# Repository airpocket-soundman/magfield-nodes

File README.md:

# magfield-nodes

> Magnetic-field visualization with ~100 coin-cell-sized LED nodes — a grid of tiny boards that turn invisible magnetic-field distortion into light.
> コインセル大の小さな基板を約100個並べ、目に見えない磁場の歪みや揺らぎを「光の色」として見える化するプロジェクトです。

## 概要

ボタン電池くらいの小さな基板（ノード）に、地磁気センサー・小さなマイコン・RGB LEDを載せ、磁場の向きや強さに応じてLEDの色をリアルタイムに変えます。この基板を10メートル四方に1メートル間隔で約100個並べると、その空間の中で磁場がどう歪んでいるか・揺らいでいるかが、光の分布として目で見えるようになります。

## ノード基板（v3）

### 主な仕様

| 項目 | 内容 |
|---|---|
| 基板サイズ | 32 × 32 mm、2層、表面実装は片面のみ（コネクタと電池ホルダーは裏面） |
| マイコン | ATtiny1616-MNR（電池直結で動作、書き込みはUPDI） |
| 地磁気センサー | Bosch BMM150（I2C、3.0V LDOレールから給電） |
| LED | WS2812B-MINI ×1（磁場の向き・変化を色で表示） |
| 電池 | LIR2032 充電式コインセル（約40mAh、公称3.6/3.7V）※LCSCに取り扱いがないため別途調達 |
| 電池保護 | DW01A + FS8205A（過放電保護を全ノードに搭載） |
| 電池ホルダー | MYOUNG MY-2032-10（裏面） |
| 接続 | JST PH 4ピン（Grove互換形状、裏面・下辺）: GND / 充電(VBAT) / UPDI / ID予備 |

### 設計のポイント

- **充電は基板側に載せない**: 充電管理は外部の充電ボード側に集約し、ノードは充電中は電源OFF。充電ラインは負荷スイッチの手前から取るため、充電中は充電回路だけが電池につながります。
- **磁気的な配慮**: センサーは電流経路・電池から最も遠い基板の角に配置し、LED（最大電流源）の配線ループ面積を小さくしています。基板自身が作る磁場のオフセットは、ノードごとの校正で吸収する前提です。
- **書き込み**: UPDIパッド（表面）とJST PHコネクタ経由の両方から書き込み可能。専用書き込み機なしで済むよう、充電ボード経由の書き込みも計画しています。

詳細は [node/DESIGN.md](node/DESIGN.md) を参照してください。

## 充電ボード（ハブ、WIP）

ノード10台をまとめて充電・管理するボードです。頭脳は持たせず、M5StackからPort A（I2C）経由で制御する構成にしています。

- 充電IC ×10（MCP73831、約40mA = 1C）、80〜90%で止めるカットオフ制御
- I2C GPIOエクスパンダ＋アナログ切替＋I2C ADCで、全チャンネルの状態監視と電池電圧読み取り
- UPDI信号の切替により、差したノードへのプログラム書き込みにも対応予定
- 充電用電源はボード側のUSB-C 5V入力から供給

KiCadファイル一式は [charge-board/](charge-board/) に追加済みです（4層基板、WIP — DRC残件あり、未発注。現状は charge-board/DESIGN.md 参照）。

## ステータス（2026-10-30時点）

- ノード基板 v3: 設計完了（KiCad 8、DRCエラー0・未接続0）。**未発注** — 発注前に要確認の項目が [node/DESIGN.md](node/DESIGN.md) に残っています（FS8205Aのピン配置、ホルダーのランドパターン、WS2812B-MINIのパッド順、LDOとスライドスイッチのLCSC型番など）。
- 充電ボード: KiCadファイル追加済み（4層、WIP）。DRC残件（未接続1件・クリアランス4件）があり未発注。
- ファームウェア（ノード／M5Stack側とも）: 未着手。要件はDESIGN.mdに記録しています（常時点灯／点滅モード、感度マッピングのパラメータ化など）。

## リポジトリ構成

```
.
├── README.md            このファイル
├── LICENSE              MIT
├── bom-estimate.md      ノード基板のBOM見積もり（LCSC価格ベース）
├── node/                ノード基板 (KiCad 8)
│   ├── magfield-node.kicad_pro / .kicad_sch / .kicad_pcb
│   ├── DESIGN.md        設計仕様・判断記録・未確認事項
│   ├── MAGFIELD.pretty/ カスタムフットプリント（基板埋め込み分から復元）
│   ├── fp-lib-table
│   ├── gerbers/         製造用ガーバー（v3）
│   └── iterations/      レイアウト図・外観図
└── charge-board/        充電ボード（ハブ、KiCadファイル一式、WIP）
```

## ライセンス

MIT License — [LICENSE](LICENSE) を参照してください。

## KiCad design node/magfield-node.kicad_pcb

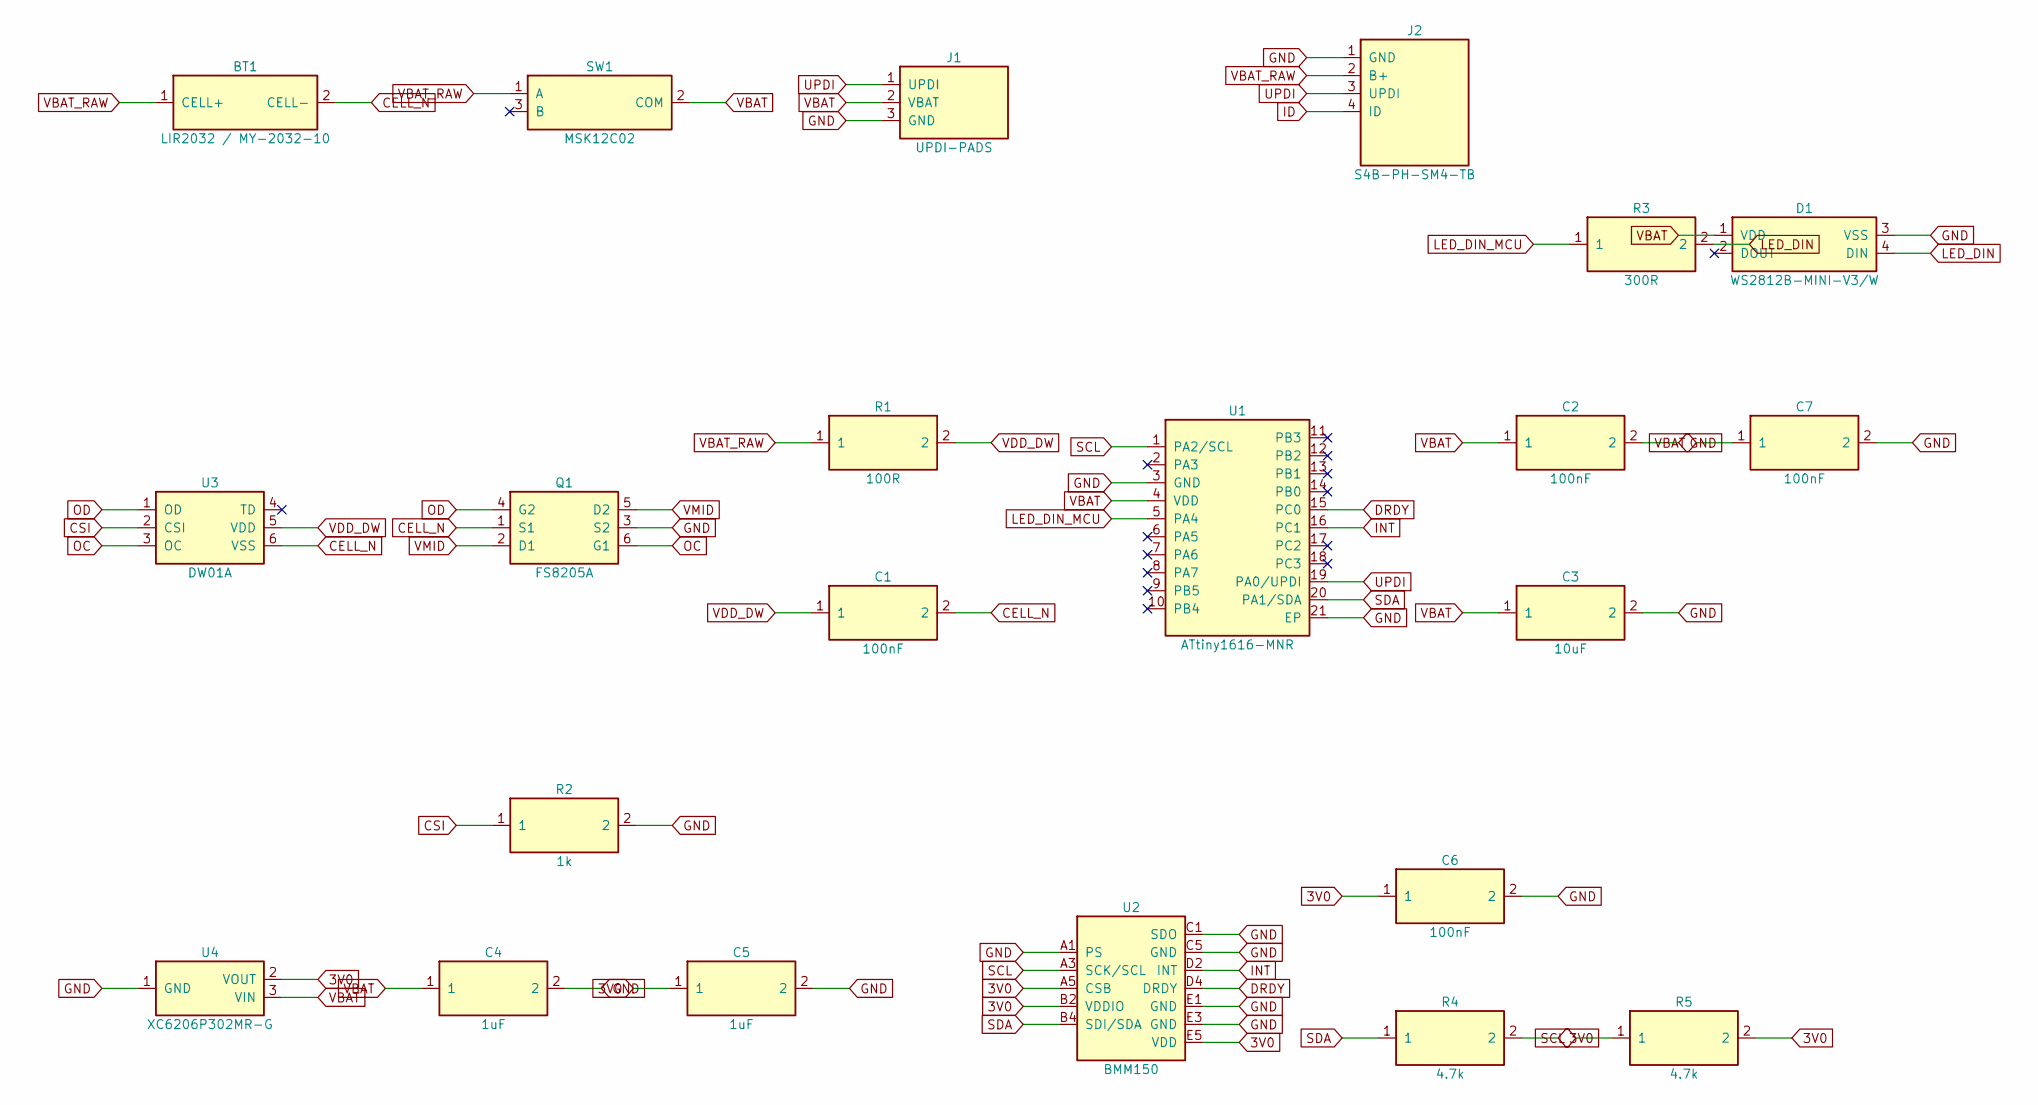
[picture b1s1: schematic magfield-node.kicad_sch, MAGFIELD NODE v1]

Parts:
BT1: LIR2032 / MY-2032-10; MY-2032-10; MPN MY-2032-10; LCSC C964827
C1, C2, C6, C7: 100nF; C_0603_1608Metric; MPN CL10B104KB8NNNC; LCSC C1591
C3: 10uF; C_0603_1608Metric; MPN CL10A106KP8NNNC; LCSC C19702
C4, C5: 1uF; C_0603_1608Metric; MPN CL10A105KB8NNNC; LCSC C15849
D1: WS2812B-MINI-V3/W; WS2812B-MINI; MPN WS2812B-MINI-V3/W; LCSC C527089
J1: UPDI-PADS; UPDI_PADS
J2: S4B-PH-SM4-TB; JST_PH_S4B-PH-SM4-TB_1x04-1MP_P2.00mm_Horizontal; MPN S4B-PH-SM4-TB(LF)(SN); LCSC C265102
Q1: FS8205A; SOT-23-6; MPN FS8205A; LCSC C2830320
R1: 100R; R_0603_1608Metric; MPN 0603WAF1000T5E; LCSC C22775
R2: 1k; R_0603_1608Metric; MPN 0603WAF1001T5E; LCSC C21190
R3: 300R; R_0603_1608Metric; MPN 0603WAF3000T5E; LCSC C23025
R4, R5: 4.7k; R_0603_1608Metric; MPN 0603WAF4701T5E; LCSC C23162
SW1: MSK12C02; SW_MSK12C02; MPN MSK12C02; LCSC C431540
U1: ATtiny1616-MNR; VQFN-20-1EP_3x3mm_P0.4mm_EP1.7x1.7mm; MPN ATTINY1616-MNR; LCSC C507118
U2: BMM150; BMM150_WLCSP12; MPN BMM150; LCSC C171681
U3: DW01A; SOT-23-6; MPN DW01A; LCSC C42459937
U4: XC6206P302MR-G; SOT-23; MPN XC6206P302MR-G; LCSC C9972

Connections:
3V0: C5.1, C6.1, R4.2, R5.2, U2.A5 (CSB), U2.B2 (VDDIO), U2.E5 (VDD), U4.2 (VOUT)
CELL_N: BT1.2 (CELL-), C1.2, Q1.1 (S1), U3.6 (VSS)
CSI: R2.1, U3.2 (CSI)
DRDY: U1.15 (PC0), U2.D4 (DRDY)
GND: C2.2, C3.2, C4.2, C5.2, C6.2, C7.2, D1.3 (VSS), J1.3 (GND), J2.1 (GND), J2.MP, Q1.3 (S2), R2.2, U1.3 (GND), U1.21 (EP), U2.A1 (PS), U2.C1 (SDO), U2.C5 (GND), U2.E1 (GND), U2.E3 (GND), U4.1 (GND)
ID: J2.4 (ID)
INT: U1.16 (PC1), U2.D2 (INT)
LED_DIN: D1.4 (DIN), R3.2
LED_DIN_MCU: R3.1, U1.5 (PA4)
OC: Q1.6 (G1), U3.3 (OC)
OD: Q1.4 (G2), U3.1 (OD)
SCL: R5.1, U1.1 (PA2/SCL), U2.A3 (SCK/SCL)
SDA: R4.1, U1.20 (PA1/SDA), U2.B4 (SDI/SDA)
UPDI: J1.1 (UPDI), J2.3 (UPDI), U1.19 (PA0/UPDI)
VBAT: C2.1, C3.1, C4.1, C7.1, D1.1 (VDD), J1.2 (VBAT), SW1.2 (COM), U1.4 (VDD), U4.3 (VIN)
VBAT_RAW: BT1.1 (CELL+), J2.2 (B+), R1.1, SW1.1 (A)
VDD_DW: C1.1, R1.2, U3.5 (VDD)
VMID: Q1.2 (D1), Q1.5 (D2)

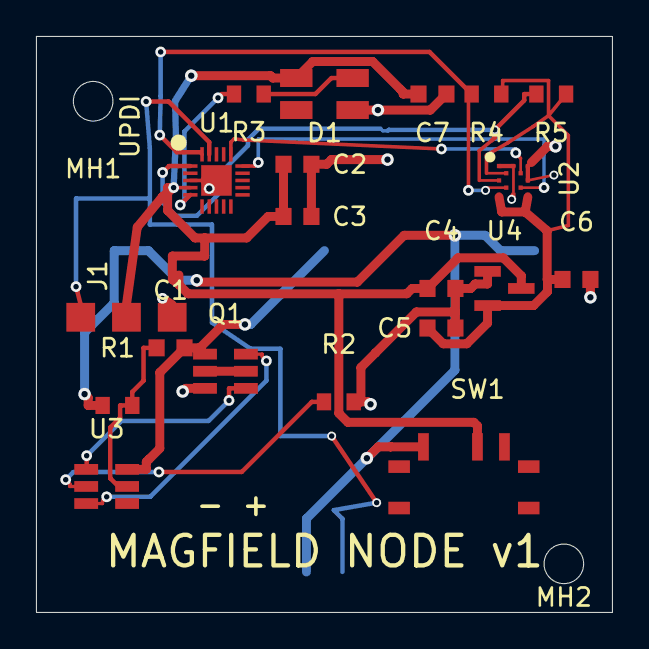
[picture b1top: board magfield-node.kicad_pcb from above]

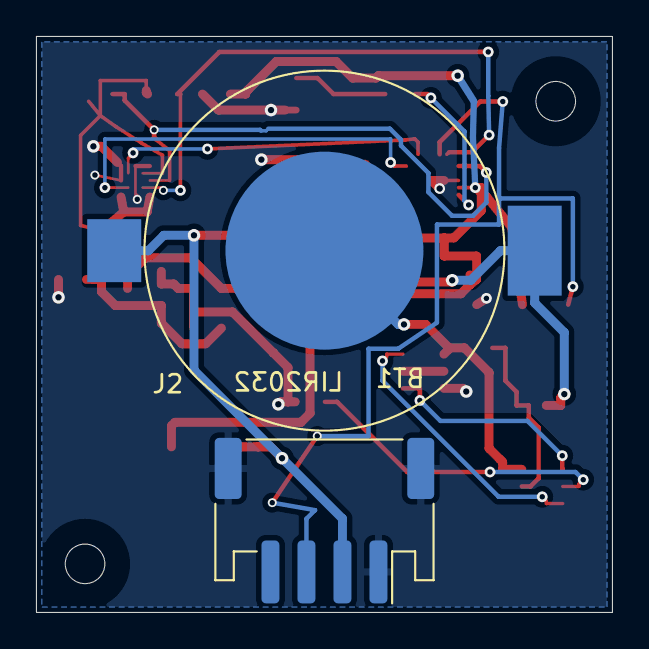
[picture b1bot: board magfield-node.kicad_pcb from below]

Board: 2 copper layers, 32.0 x 32.0 mm, 24 parts (2 on the bottom side), 17 nets.

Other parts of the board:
MH1, MH2: MountingHole_2.2mm_M2

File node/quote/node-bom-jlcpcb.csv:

Comment,Designator,Footprint,LCSC Part #,Quantity
MY-2032-10 battery holder for LIR2032 (cell NOT included),BT1,MY-2032-10,C964827,1
100nF,"C1,C2,C6,C7",C_0603_1608Metric,C1591,4
10uF,C3,C_0603_1608Metric,C19702,1
1uF,"C4,C5",C_0603_1608Metric,C15849,2
WS2812B-MINI-V3/W,D1,WS2812B-MINI,C527089,1
S4B-PH-SM4-TB,J2,JST_PH_S4B-PH-SM4-TB_1x04-1MP_P2.00mm_Horizontal,C265102,1
FS8205A,Q1,SOT-23-6,C2830320,1
100R,R1,R_0603_1608Metric,C22775,1
1k,R2,R_0603_1608Metric,C21190,1
300R,R3,R_0603_1608Metric,C23025,1
4.7k,"R4,R5",R_0603_1608Metric,C23162,2
MSK12C02 SPDT slide switch (SHOU HAN),SW1,SW_MSK12C02,C431540,1
ATtiny1616-MNR,U1,VQFN-20-1EP_3x3mm_P0.4mm_EP1.7x1.7mm,C507118,1
BMM150,U2,BMM150_WLCSP12,C171681,1
DW01A,U3,SOT-23-6,C42459937,1
XC6206P302MR-G,U4,SOT-23,C9972,1
